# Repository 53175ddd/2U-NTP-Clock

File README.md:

# 自作 2U NTP 時計

KiCAD 8 にて開発しています．

## 取扱説明書

現在開発中のため，完成次第書きます．

## ファームウェアアップデート方法

> [!NOTE]
> 開発には Arduino 環境を使用しています．手順 0 に従って Arduino IDE をインストールしてください．

> [!NOTE]
> 既にインストール済みの場合は飛ばしてください．

### 手順 0 - 1｜Arduino IDE のインストールと初期設定

以下のリンクより，Arduino IDE のインストーラをダウンロードして，インストールします．

<https://arduino.cc/en/software/>

インストールしたら，[Ctrl] + [,] で基本設定を開き，`Luanguage:` の右のプルダウンメニューを展開して「日本語」を選択し，[OK] を押して日本語化します．  
その真下のチェックボックス 2 つにチェックを入れておくと良いでしょう．  
その後，以下の URL を「追加のボードマネージャの URL:」の欄にコピペします．

```
https://raw.githubusercontent.com/espressif/arduino-esp32/gh-pages/package_esp32_dev_index.json
```

### 手順 0 - 2｜ESP32 の開発環境のインストール

Arduino IDE のインストールができたら，ESP32 用の開発環境をインストールします．

[Ctrl] + [Shift] + [B] を押してボードマネージャを開き，検索窓に「ESP32」と入力します．  
すると「esp32 by Espressif Systems」がでてくるので，最新版をインストールします．

> [!WARNING]
> 結構時間がかかります．

### 手順 1 - 1｜GitHub リポジトリのクローン

Git コマンドあるいは GitHub Desktop などを用いて GitHub リポジトリをクローンするか，Zip でダウンロードし，任意のディレクトリに展開します．

### 手順 1 - 2｜Arduino スケッチの起動と修正

`./2U-NTP-Clock.ino` を開きます．

以下のような記述があるので，それをお使いの環境に合わせて変更します．

```cpp
/* Wi-Fi アクセスポイントの設定 */
/* "" の中身を変更してください． */

char ssid[] = "YOUR-SSID-HERE";
char psk[]  = "YOUR-PSK-HERE";
```

### 手順 1 - 3｜PC に接続

USB Type-C ケーブルで コントローラ（M5 Stamp-S3）と PC を接続します．

### 手順 1 - 4｜ビルドと書き込み

ボード選択画面から「M5StampS3」を選択し，COM ポートも選択します．

[Ctrl] + [U] でビルド & フラッシュします．

### 手順 2 - 1｜動作確認

ファームウェアを書き込むと自動的に再起動します．  
再起動後，正しく時刻同期ができるかを確認してください．

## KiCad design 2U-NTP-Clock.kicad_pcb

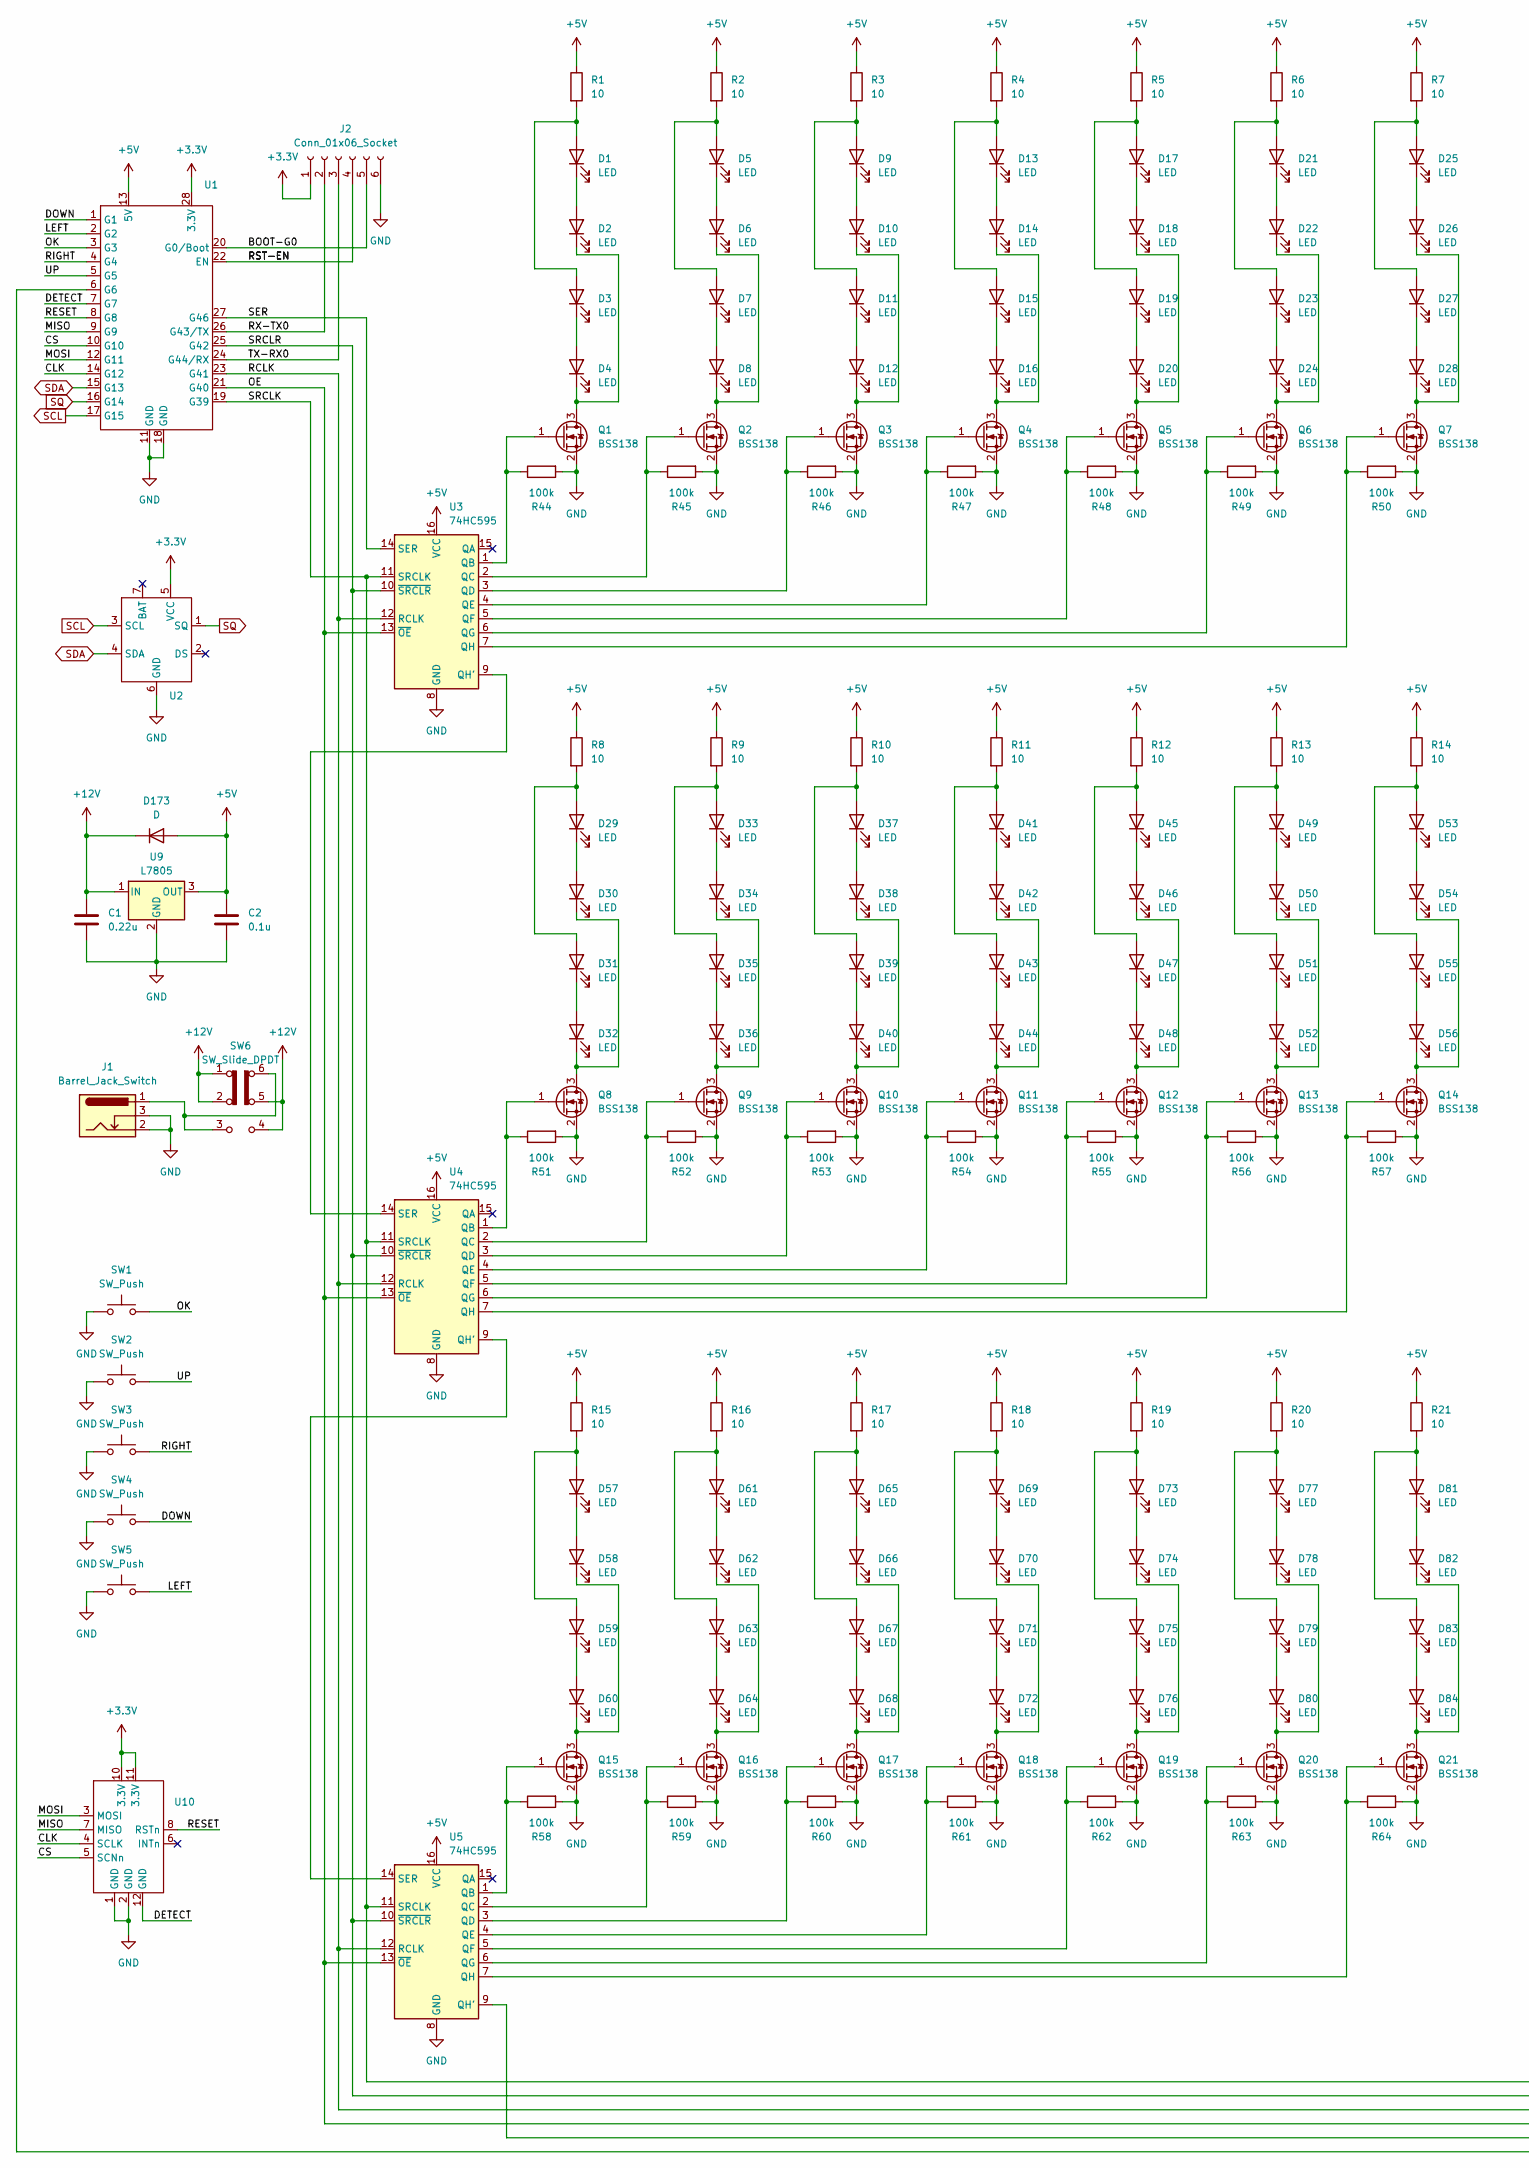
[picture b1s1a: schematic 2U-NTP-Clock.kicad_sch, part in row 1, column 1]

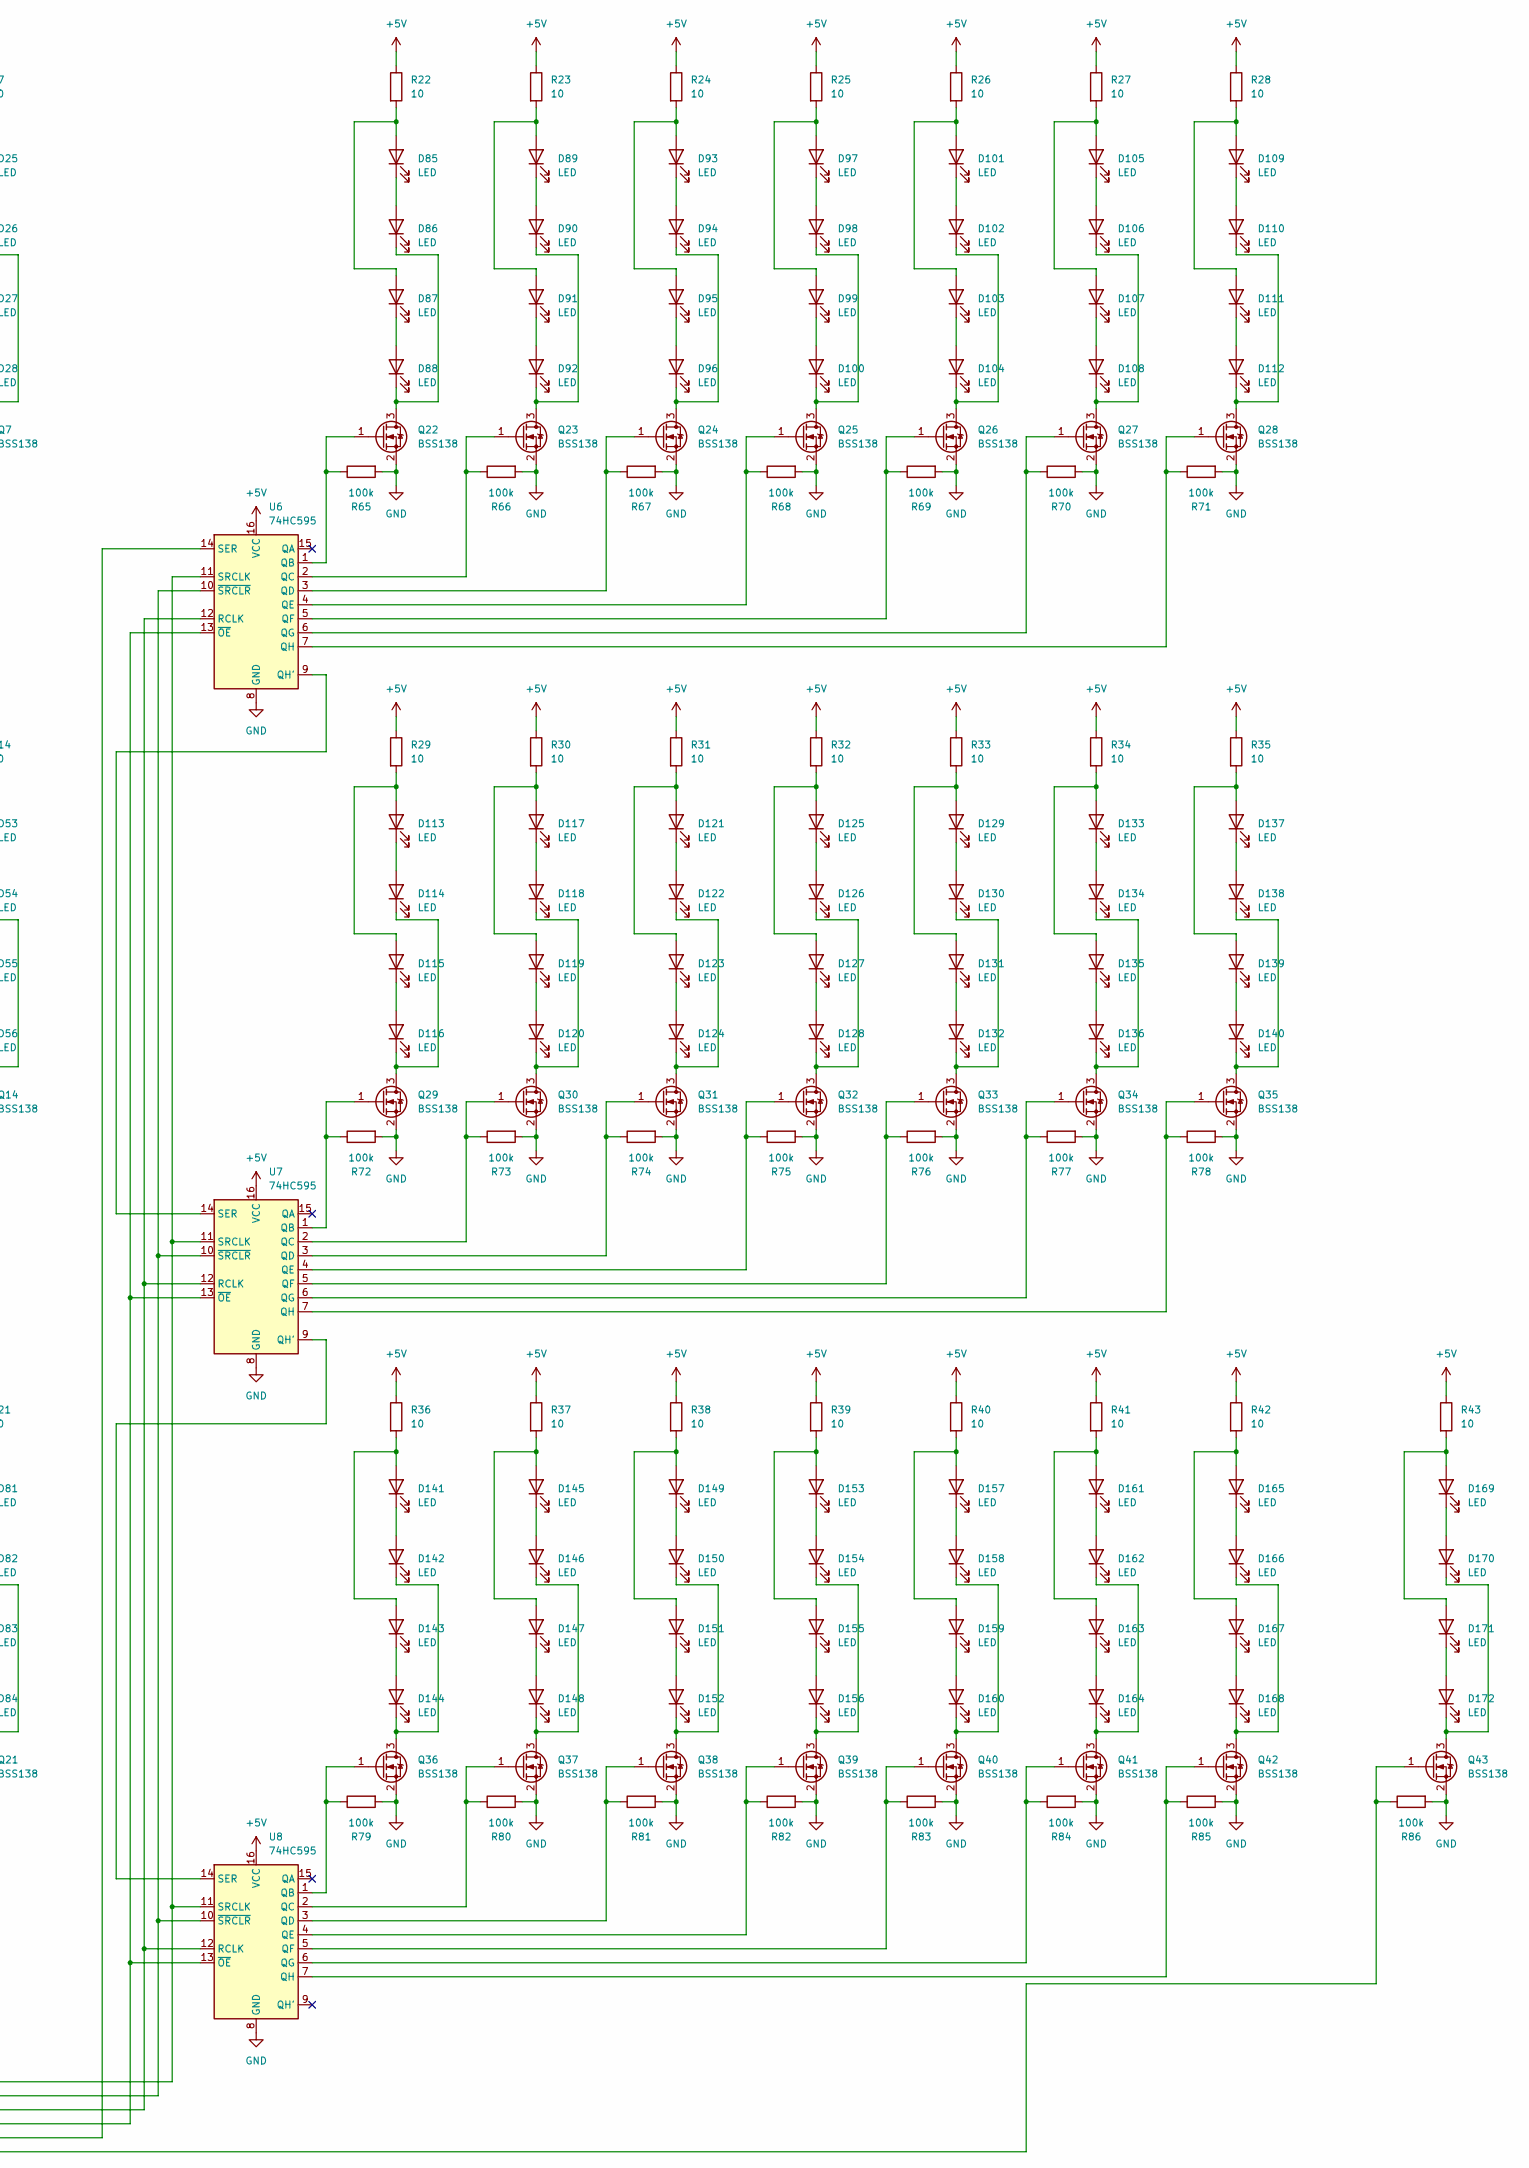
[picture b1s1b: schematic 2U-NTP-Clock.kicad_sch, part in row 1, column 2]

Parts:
C1: 0.22u; C_0603_1608Metric; LCSC C14663
C2: 0.1u; C_0603_1608Metric; LCSC C14663
D1, D2, D3, D4, D5, D6, D7, D8, D9, D10, D11, D12, D13, D14, D15, D16, D17, D18, D19, D20, D21, D22, D23, D24, D25, D26, D27, D28, D29, D30, D31, D32, D33, D34, D35, D36, D37, D38, D39, D40, D41, D42, D43, D44, D45, D46, D47, D48, D49, D50, D51, D52, D53, D54, D55, D56, D57, D58, D59, D60, D61, D62, D63, D64, D65, D66, D67, D68, D69, D70, D71, D72, D73, D74, D75, D76, D77, D78, D79, D80, D81, D82, D83, D84, D85, D86, D87, D88, D89, D90, D91, D92, D93, D94, D95, D96, D97, D98, D99, D100, D101, D102, D103, D104, D105, D106, D107, D108, D109, D110, D111, D112, D113, D114, D115, D116, D117, D118, D119, D120, D121, D122, D123, D124, D125, D126, D127, D128, D129, D130, D131, D132, D133, D134, D135, D136, D137, D138, D139, D140, D141, D142, D143, D144, D145, D146, D147, D148, D149, D150, D151, D152, D153, D154, D155, D156, D157, D158, D159, D160, D161, D162, D163, D164, D165, D166, D167, D168, D169, D170, D171, D172: LED; LED_D5.0mm; LCSC C2895492
D173: D; D_SOD-523; LCSC C232841
J1: Barrel_Jack_Switch; BarrelJack_Horizontal
J2: Conn_01x06_Socket; PinSocket_1x06_P2.54mm_Vertical
Q1, Q2, Q3, Q4, Q5, Q6, Q7, Q8, Q9, Q10, Q11, Q12, Q13, Q14, Q15, Q16, Q17, Q18, Q19, Q20, Q21, Q22, Q23, Q24, Q25, Q26, Q27, Q28, Q29, Q30, Q31, Q32, Q33, Q34, Q35, Q36, Q37, Q38, Q39, Q40, Q41, Q42, Q43: BSS138; SOT-23; LCSC C82045
R1, R2, R3, R4, R5, R6, R7, R8, R9, R10, R11, R12, R13, R14, R15, R16, R17, R18, R19, R20, R21, R22, R23, R24, R25, R26, R27, R28, R29, R30, R31, R32, R33, R34, R35, R36, R37, R38, R39, R40, R41, R42, R43: 10; R_0603_1608Metric; LCSC C109318
R44, R45, R46, R47, R48, R49, R50, R51, R52, R53, R54, R55, R56, R57, R58, R59, R60, R61, R62, R63, R64, R65, R66, R67, R68, R69, R70, R71, R72, R73, R74, R75, R76, R77, R78, R79, R80, R81, R82, R83, R84, R85, R86: 100k; R_0603_1608Metric; LCSC C14675
SW1, SW2, SW3, SW4, SW5: SW_Push; SW_PUSH_6mm
SW6: SW_Slide_DPDT; SW_E-Switch_EG1271_SPDT
U1: STAMP-S3-DIP
U2: TinyRTC_Battery_Side_Up
U3, U4, U5, U6, U7, U8: 74HC595; SOIC-16_3.9x9.9mm_P1.27mm; LCSC C5947
U9: L7805; TO-252-2; LCSC C22376607
U10: WIZ850io

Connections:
+3.3V: J2.1, U1.28 (3.3V), U2.5 (VCC), U10.10 (3.3V), U10.11 (3.3V)
+5V: C2.1, D173.2 (A), R1.1, R2.1, R3.1, R4.1, R5.1, R6.1, R7.1, R8.1, R9.1, R10.1, R11.1, R12.1, R13.1, R14.1, R15.1, R16.1, R17.1, R18.1, R19.1, R20.1, R21.1, R22.1, R23.1, R24.1, R25.1, R26.1, R27.1, R28.1, R29.1, R30.1, R31.1, R32.1, R33.1, R34.1, R35.1, R36.1, R37.1, R38.1, R39.1, R40.1, R41.1, R42.1, R43.1, U1.13 (5V), U3.16 (VCC), U4.16 (VCC), U5.16 (VCC), U6.16 (VCC), U7.16 (VCC), U8.16 (VCC), U9.3 (OUT)
+12V: C1.1, D173.1 (K), SW6.1 (A), SW6.2 (B), SW6.4 (A), SW6.5 (B), U9.1 (IN)
/BOOT-G0: J2.5, U1.20 (G0/Boot)
/CLK: U1.14 (G12), U10.4 (SCLK)
/CS: U1.10 (G10), U10.5 (SCNn)
/DETECT: U1.7 (G7), U10.12 (GND)
/DOWN: SW4.1, U1.1 (G1)
/LEFT: SW5.1, U1.2 (G2)
/MISO: U1.9 (G9), U10.7 (MISO)
/MOSI: U1.12 (G11), U10.3 (MOSI)
/OE: U1.21 (G40), U3.13 (~OE), U4.13 (~OE), U5.13 (~OE), U6.13 (~OE), U7.13 (~OE), U8.13 (~OE)
/OK: SW1.1, U1.3 (G3)
/RCLK: U1.23 (G41), U3.12 (RCLK), U4.12 (RCLK), U5.12 (RCLK), U6.12 (RCLK), U7.12 (RCLK), U8.12 (RCLK)
/RESET: U1.8 (G8), U10.8 (RSTn)
/RIGHT: SW3.1, U1.4 (G4)
/RX-TX0: J2.2, U1.26 (G43/TX)
/SER: U1.27 (G46), U3.14 (SER)
/SRCLK: U1.19 (G39), U3.11 (SRCLK), U4.11 (SRCLK), U5.11 (SRCLK), U6.11 (SRCLK), U7.11 (SRCLK), U8.11 (SRCLK)
/SRCLR: U1.25 (G42), U3.10 (~SRCLR), U4.10 (~SRCLR), U5.10 (~SRCLR), U6.10 (~SRCLR), U7.10 (~SRCLR), U8.10 (~SRCLR)
/TX-RX0: J2.3, U1.24 (G44/RX)
/UP: SW2.1, U1.5 (G5)
GND: C1.2, C2.2, J1.2, J1.3, J2.6, Q1.2 (S), Q2.2 (S), Q3.2 (S), Q4.2 (S), Q5.2 (S), Q6.2 (S), Q7.2 (S), Q8.2 (S), Q9.2 (S), Q10.2 (S), Q11.2 (S), Q12.2 (S), Q13.2 (S), Q14.2 (S), Q15.2 (S), Q16.2 (S), Q17.2 (S), Q18.2 (S), Q19.2 (S), Q20.2 (S), Q21.2 (S), Q22.2 (S), Q23.2 (S), Q24.2 (S), Q25.2 (S), Q26.2 (S), Q27.2 (S), Q28.2 (S), Q29.2 (S), Q30.2 (S), Q31.2 (S), Q32.2 (S), Q33.2 (S), Q34.2 (S), Q35.2 (S), Q36.2 (S), Q37.2 (S), Q38.2 (S), Q39.2 (S), Q40.2 (S), Q41.2 (S), Q42.2 (S), Q43.2 (S), R44.2, R45.2, R46.2, R47.2, R48.2, R49.2, R50.2, R51.2, R52.2, R53.2, R54.2, R55.2, R56.2, R57.2, R58.2, R59.2, R60.2, R61.2, R62.2, R63.2, R64.2, R65.2, R66.2, R67.2, R68.2, R69.2, R70.2, R71.2, R72.2, R73.2, R74.2, R75.2, R76.2, R77.2, R78.2, R79.2, R80.2, R81.2, R82.2, R83.2, R84.2, R85.2, R86.2, SW1.2, SW2.2, SW3.2, SW4.2, SW5.2, U1.11 (GND), U1.18 (GND), U2.6 (GND), U3.8 (GND), U4.8 (GND), U5.8 (GND), U6.8 (GND), U7.8 (GND), U8.8 (GND), U9.2 (GND), U10.1 (GND), U10.2 (GND)
unnamed: D1.2 (A), D3.2 (A), R1.2
unnamed: D1.1 (K), D2.2 (A)
unnamed: D2.1 (K), D4.1 (K), Q1.3 (D)
unnamed: D3.1 (K), D4.2 (A)
unnamed: D5.2 (A), D7.2 (A), R2.2
unnamed: D5.1 (K), D6.2 (A)
unnamed: D6.1 (K), D8.1 (K), Q2.3 (D)
unnamed: D7.1 (K), D8.2 (A)
unnamed: D9.1 (K), D10.2 (A)
unnamed: D10.1 (K), D12.1 (K), Q3.3 (D)
unnamed: D9.2 (A), D11.2 (A), R3.2
unnamed: D11.1 (K), D12.2 (A)
unnamed: D13.2 (A), D15.2 (A), R4.2
unnamed: D13.1 (K), D14.2 (A)
unnamed: D14.1 (K), D16.1 (K), Q4.3 (D)
unnamed: D15.1 (K), D16.2 (A)
unnamed: D17.2 (A), D19.2 (A), R5.2
unnamed: D17.1 (K), D18.2 (A)
unnamed: D18.1 (K), D20.1 (K), Q5.3 (D)
unnamed: D19.1 (K), D20.2 (A)
unnamed: D21.2 (A), D23.2 (A), R6.2
unnamed: D21.1 (K), D22.2 (A)
unnamed: D22.1 (K), D24.1 (K), Q6.3 (D)
unnamed: D23.1 (K), D24.2 (A)
unnamed: D25.2 (A), D27.2 (A), R7.2
unnamed: D25.1 (K), D26.2 (A)
unnamed: D26.1 (K), D28.1 (K), Q7.3 (D)
unnamed: D27.1 (K), D28.2 (A)
unnamed: D29.2 (A), D31.2 (A), R8.2
unnamed: D29.1 (K), D30.2 (A)
unnamed: D30.1 (K), D32.1 (K), Q8.3 (D)
unnamed: D31.1 (K), D32.2 (A)
unnamed: D33.2 (A), D35.2 (A), R9.2
unnamed: D33.1 (K), D34.2 (A)
unnamed: D34.1 (K), D36.1 (K), Q9.3 (D)
unnamed: D35.1 (K), D36.2 (A)
unnamed: D37.2 (A), D39.2 (A), R10.2
unnamed: D37.1 (K), D38.2 (A)
unnamed: D38.1 (K), D40.1 (K), Q10.3 (D)
unnamed: D39.1 (K), D40.2 (A)
unnamed: D41.2 (A), D43.2 (A), R11.2
unnamed: D41.1 (K), D42.2 (A)
unnamed: D42.1 (K), D44.1 (K), Q11.3 (D)
unnamed: D43.1 (K), D44.2 (A)
unnamed: D45.2 (A), D47.2 (A), R12.2
unnamed: D45.1 (K), D46.2 (A)
unnamed: D46.1 (K), D48.1 (K), Q12.3 (D)
unnamed: D47.1 (K), D48.2 (A)
unnamed: D49.2 (A), D51.2 (A), R13.2
unnamed: D49.1 (K), D50.2 (A)
unnamed: D50.1 (K), D52.1 (K), Q13.3 (D)
unnamed: D51.1 (K), D52.2 (A)
unnamed: D53.2 (A), D55.2 (A), R14.2
unnamed: D53.1 (K), D54.2 (A)
unnamed: D54.1 (K), D56.1 (K), Q14.3 (D)
unnamed: D55.1 (K), D56.2 (A)
unnamed: D57.2 (A), D59.2 (A), R15.2
unnamed: D57.1 (K), D58.2 (A)
unnamed: D58.1 (K), D60.1 (K), Q15.3 (D)
unnamed: D59.1 (K), D60.2 (A)
unnamed: D61.2 (A), D63.2 (A), R16.2
unnamed: D61.1 (K), D62.2 (A)
unnamed: D62.1 (K), D64.1 (K), Q16.3 (D)
unnamed: D63.1 (K), D64.2 (A)
unnamed: D65.2 (A), D67.2 (A), R17.2
unnamed: D65.1 (K), D66.2 (A)
unnamed: D66.1 (K), D68.1 (K), Q17.3 (D)
unnamed: D67.1 (K), D68.2 (A)
unnamed: D69.2 (A), D71.2 (A), R18.2
unnamed: D69.1 (K), D70.2 (A)
unnamed: D70.1 (K), D72.1 (K), Q18.3 (D)
unnamed: D71.1 (K), D72.2 (A)
unnamed: D73.2 (A), D75.2 (A), R19.2
unnamed: D73.1 (K), D74.2 (A)
unnamed: D74.1 (K), D76.1 (K), Q19.3 (D)
unnamed: D75.1 (K), D76.2 (A)
unnamed: D77.2 (A), D79.2 (A), R20.2
unnamed: D77.1 (K), D78.2 (A)
unnamed: D78.1 (K), D80.1 (K), Q20.3 (D)
unnamed: D79.1 (K), D80.2 (A)
unnamed: D81.2 (A), D83.2 (A), R21.2
unnamed: D81.1 (K), D82.2 (A)
unnamed: D82.1 (K), D84.1 (K), Q21.3 (D)
unnamed: D83.1 (K), D84.2 (A)
unnamed: D85.2 (A), D87.2 (A), R22.2
unnamed: D85.1 (K), D86.2 (A)
unnamed: D86.1 (K), D88.1 (K), Q22.3 (D)
unnamed: D87.1 (K), D88.2 (A)
unnamed: D89.2 (A), D91.2 (A), R23.2
unnamed: D89.1 (K), D90.2 (A)
unnamed: D90.1 (K), D92.1 (K), Q23.3 (D)
unnamed: D91.1 (K), D92.2 (A)
unnamed: D93.2 (A), D95.2 (A), R24.2
unnamed: D93.1 (K), D94.2 (A)
unnamed: D94.1 (K), D96.1 (K), Q24.3 (D)
unnamed: D95.1 (K), D96.2 (A)
unnamed: D97.2 (A), D99.2 (A), R25.2
unnamed: D97.1 (K), D98.2 (A)
unnamed: D99.1 (K), D100.2 (A)
unnamed: D98.1 (K), D100.1 (K), Q25.3 (D)
unnamed: D101.2 (A), D103.2 (A), R26.2
unnamed: D101.1 (K), D102.2 (A)
unnamed: D102.1 (K), D104.1 (K), Q26.3 (D)
unnamed: D103.1 (K), D104.2 (A)
unnamed: D105.2 (A), D107.2 (A), R27.2
unnamed: D105.1 (K), D106.2 (A)
unnamed: D106.1 (K), D108.1 (K), Q27.3 (D)
unnamed: D107.1 (K), D108.2 (A)
unnamed: D109.2 (A), D111.2 (A), R28.2
unnamed: D109.1 (K), D110.2 (A)
unnamed: D110.1 (K), D112.1 (K), Q28.3 (D)
unnamed: D111.1 (K), D112.2 (A)
unnamed: D113.2 (A), D115.2 (A), R29.2
unnamed: D113.1 (K), D114.2 (A)
unnamed: D114.1 (K), D116.1 (K), Q29.3 (D)
unnamed: D115.1 (K), D116.2 (A)
unnamed: D117.2 (A), D119.2 (A), R30.2
unnamed: D117.1 (K), D118.2 (A)
unnamed: D118.1 (K), D120.1 (K), Q30.3 (D)
unnamed: D119.1 (K), D120.2 (A)
unnamed: D121.2 (A), D123.2 (A), R31.2
unnamed: D121.1 (K), D122.2 (A)
unnamed: D122.1 (K), D124.1 (K), Q31.3 (D)
unnamed: D123.1 (K), D124.2 (A)
unnamed: D125.2 (A), D127.2 (A), R32.2
unnamed: D125.1 (K), D126.2 (A)
unnamed: D126.1 (K), D128.1 (K), Q32.3 (D)
unnamed: D127.1 (K), D128.2 (A)
unnamed: D129.2 (A), D131.2 (A), R33.2
unnamed: D129.1 (K), D130.2 (A)
unnamed: D130.1 (K), D132.1 (K), Q33.3 (D)
unnamed: D131.1 (K), D132.2 (A)
unnamed: D133.2 (A), D135.2 (A), R34.2
unnamed: D133.1 (K), D134.2 (A)
unnamed: D134.1 (K), D136.1 (K), Q34.3 (D)
unnamed: D135.1 (K), D136.2 (A)
unnamed: D137.2 (A), D139.2 (A), R35.2
unnamed: D137.1 (K), D138.2 (A)
unnamed: D138.1 (K), D140.1 (K), Q35.3 (D)
unnamed: D139.1 (K), D140.2 (A)
unnamed: D141.2 (A), D143.2 (A), R36.2
unnamed: D141.1 (K), D142.2 (A)
unnamed: D142.1 (K), D144.1 (K), Q36.3 (D)
unnamed: D143.1 (K), D144.2 (A)
unnamed: D145.2 (A), D147.2 (A), R37.2
unnamed: D145.1 (K), D146.2 (A)
unnamed: D146.1 (K), D148.1 (K), Q37.3 (D)
unnamed: D147.1 (K), D148.2 (A)
unnamed: D149.2 (A), D151.2 (A), R38.2
unnamed: D149.1 (K), D150.2 (A)
unnamed: D150.1 (K), D152.1 (K), Q38.3 (D)
unnamed: D151.1 (K), D152.2 (A)
unnamed: D153.2 (A), D155.2 (A), R39.2
unnamed: D153.1 (K), D154.2 (A)
unnamed: D154.1 (K), D156.1 (K), Q39.3 (D)
unnamed: D155.1 (K), D156.2 (A)
unnamed: D157.2 (A), D159.2 (A), R40.2
unnamed: D157.1 (K), D158.2 (A)
unnamed: D158.1 (K), D160.1 (K), Q40.3 (D)
unnamed: D159.1 (K), D160.2 (A)
unnamed: D161.2 (A), D163.2 (A), R41.2
unnamed: D161.1 (K), D162.2 (A)
unnamed: D162.1 (K), D164.1 (K), Q41.3 (D)
unnamed: D163.1 (K), D164.2 (A)
unnamed: D165.2 (A), D167.2 (A), R42.2
unnamed: D165.1 (K), D166.2 (A)
unnamed: D166.1 (K), D168.1 (K), Q42.3 (D)
unnamed: D167.1 (K), D168.2 (A)
unnamed: D169.2 (A), D171.2 (A), R43.2
unnamed: D169.1 (K), D170.2 (A)
unnamed: D170.1 (K), D172.1 (K), Q43.3 (D)
unnamed: D171.1 (K), D172.2 (A)
unnamed: J1.1, SW6.3 (C), SW6.6 (C)
unnamed: J2.4, U1.22 (EN)
unnamed: Q1.1 (G), R44.1, U3.1 (QB)
unnamed: Q2.1 (G), R45.1, U3.2 (QC)
unnamed: Q3.1 (G), R46.1, U3.3 (QD)
unnamed: Q4.1 (G), R47.1, U3.4 (QE)
unnamed: Q5.1 (G), R48.1, U3.5 (QF)
unnamed: Q6.1 (G), R49.1, U3.6 (QG)
unnamed: Q7.1 (G), R50.1, U3.7 (QH)
unnamed: Q8.1 (G), R51.1, U4.1 (QB)
unnamed: Q9.1 (G), R52.1, U4.2 (QC)
unnamed: Q10.1 (G), R53.1, U4.3 (QD)
unnamed: Q11.1 (G), R54.1, U4.4 (QE)
unnamed: Q12.1 (G), R55.1, U4.5 (QF)
unnamed: Q13.1 (G), R56.1, U4.6 (QG)
unnamed: Q14.1 (G), R57.1, U4.7 (QH)
unnamed: Q15.1 (G), R58.1, U5.1 (QB)
unnamed: Q16.1 (G), R59.1, U5.2 (QC)
unnamed: Q17.1 (G), R60.1, U5.3 (QD)
unnamed: Q18.1 (G), R61.1, U5.4 (QE)
unnamed: Q19.1 (G), R62.1, U5.5 (QF)
unnamed: Q20.1 (G), R63.1, U5.6 (QG)
unnamed: Q21.1 (G), R64.1, U5.7 (QH)
unnamed: Q22.1 (G), R65.1, U6.1 (QB)
unnamed: Q23.1 (G), R66.1, U6.2 (QC)
unnamed: Q24.1 (G), R67.1, U6.3 (QD)
unnamed: Q25.1 (G), R68.1, U6.4 (QE)
unnamed: Q26.1 (G), R69.1, U6.5 (QF)
unnamed: Q27.1 (G), R70.1, U6.6 (QG)
unnamed: Q28.1 (G), R71.1, U6.7 (QH)
unnamed: Q29.1 (G), R72.1, U7.1 (QB)
unnamed: Q30.1 (G), R73.1, U7.2 (QC)
unnamed: Q31.1 (G), R74.1, U7.3 (QD)
unnamed: Q32.1 (G), R75.1, U7.4 (QE)
unnamed: Q33.1 (G), R76.1, U7.5 (QF)
unnamed: Q34.1 (G), R77.1, U7.6 (QG)
unnamed: Q35.1 (G), R78.1, U7.7 (QH)
unnamed: Q36.1 (G), R79.1, U8.1 (QB)
unnamed: Q37.1 (G), R80.1, U8.2 (QC)
unnamed: Q38.1 (G), R81.1, U8.3 (QD)
unnamed: Q39.1 (G), R82.1, U8.4 (QE)
unnamed: Q40.1 (G), R83.1, U8.5 (QF)
unnamed: Q41.1 (G), R84.1, U8.6 (QG)
unnamed: Q42.1 (G), R85.1, U8.7 (QH)
unnamed: Q43.1 (G), R86.1, U1.6 (G6)
unnamed: U3.9 (QH'), U4.14 (SER)
unnamed: U4.9 (QH'), U5.14 (SER)
unnamed: U5.9 (QH'), U6.14 (SER)
unnamed: U6.9 (QH'), U7.14 (SER)
unnamed: U7.9 (QH'), U8.14 (SER)
SCL: U1.17 (G15), U2.3 (SCL)
SDA: U1.15 (G13), U2.4 (SDA)
SQ: U1.16 (G14), U2.1 (SQ)

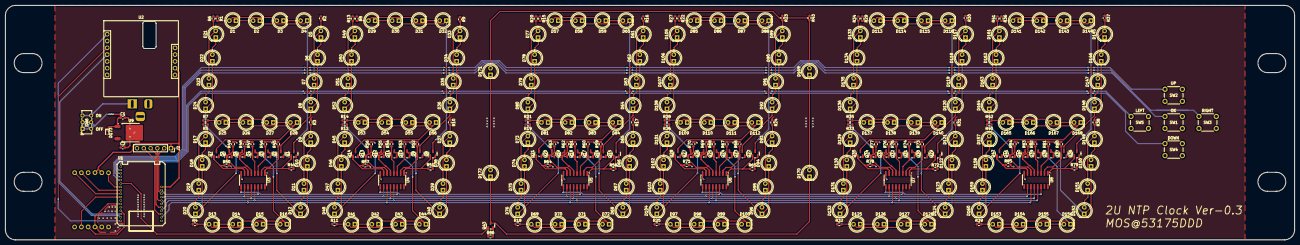
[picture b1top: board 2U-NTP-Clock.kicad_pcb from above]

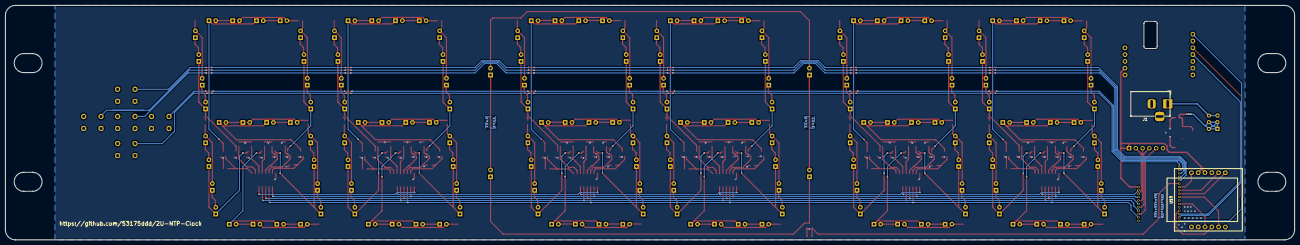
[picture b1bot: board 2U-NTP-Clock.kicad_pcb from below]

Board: 2 copper layers, 482.6 x 87.8 mm, 322 parts (2 on the bottom side), 248 nets.

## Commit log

2025-04-11 PJ 作成
2025-04-11 基板外形作成
2025-04-11 RTC のシンボルとフットプリント追加
2025-04-11 シンボル・フットプリント読み込み
2025-04-11 StampS3 追加
2025-04-11 回路図作成
2025-04-11 回路図書いた
2025-04-12 トランジスタ以外配置した
2025-04-12 配線した
2025-04-12 仕上げた
2025-04-12 製造データ吐き出し
2025-04-12 スイッチの追加と配置配線修正
2025-04-12 わすれてた GND を繋いで製造データ出力
2025-04-12 README をざっくり書いた
2025-04-12 ベタ塗りの範囲を広げた
2025-04-13 コードに合わせて変更
2025-04-14 Eth モジュールのシンボル作成
2025-04-14 デバッグポート・Eth PHY の実装
2025-04-14 Eth PHY モジュールのフットプリント作った
2025-04-14 追加部品にフットプリント割り当て
2025-04-14 Ethernet とデバッグポート乗せた
2025-04-14 邪魔なシルクを削除
2025-04-14 GND つながってなかった
2025-04-14 via の径を変更
2025-04-14 部品の割り当てを変更
2025-04-16 検証用プログラム作成
2025-04-16 ちょろっと書いた
2025-04-16 多分いらんかった
2025-04-16 AP のセットアップ処理を更新
2025-04-16 Web サーバの構成
2025-04-16 IP アドレスを変更
    ESP32 にちなんで第三オクテットを `32` に
2025-04-16 Web サーバを用意
2025-04-16 文字化け対策
2025-04-16 送信内容を出力
2025-04-16 変数なくして直接埋め込み
2025-04-17 NTP サーバの項目追加
2025-04-17 設定保存後，自動で再起動
2025-04-17 インクルードファイル追加
2025-04-17 コメント修正
2025-04-17 コンフィグの投入と再起動，自動接続に対応
2025-04-18 RTC 関係の処理を追加
2025-04-18 条件式の中に処理を移した
2025-04-18 操作用スイッチを移設
2025-04-18 タイムゾーン設定に対応
2025-04-18 改行追加
2025-04-18 表示内容の日本語化
2025-04-18 冗長な処理の削除
2025-05-02 配線修正
2025-05-02 基板配線修正
2025-05-02 スイッチ位置変更
2025-05-02 基板概形修正
2025-05-02 シルクのバージョンアップ
2025-05-02 テストコードアップデート
2025-05-02 コンフリクト修正
2025-05-04 アップデート
    ランドの径の変更
    配線取り回しの変更
    など
2025-05-04 ベタの取り回しをいい感じにした
2025-05-13 ベタ修正
2025-06-21 また回路間違えてたので修正
2025-06-21 手動修正
2025-06-21 破綻箇所修正
2025-06-21 AW 修正
2025-06-21 穴寸法調整
2025-06-21 バージョンアップ
2025-06-28 MOSFET のプルダウン抵抗を追加
2025-06-28 PD抵抗配置配線
2025-06-28 EdgeCut エラーの修正
2026-02-06 file replace to correct path
